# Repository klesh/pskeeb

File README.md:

# Portable Split Keyboard

## Features

- Tenting design - good for RSI symptoms
- Stackable - portable
- 36 keys columnar layout - less movement when typing
- Trackpoint support

## Designs

- [pskeeb1 gateron ks27](pskeeb1_gateron_ks27): Mainly designed for Gateron KS27 low profile switches, Blackpill controller, Diodeless
- [pskeeb2 express](pskeeb2_express): All Kinds of switches, Blackpill controller, Diodeless, 9.2x9.2cm PCB
- [pskeeb3 cherry hotswap](pskeeb3_cherry_hotswap): Cherry MX Switch, Raspberry Pi Pico, Diodeless
- [pskeeb4 gateron low profile ks27 hotswap](pskeeb4_gtr_lp_ks27_hotswap): Gateron Low Profile Switch, RP2040-Zero
- [pskeeb5 bluetooth kaihl choc v1/v2 hotswap](pskeeb5_bluetooth_choc_hotswap): Kaihl Choc v1/v2 Low Profile Switch, nice!nano v2

## Assembly

#### Trackpoint

1. Follow [this great guide](https://github.com/alonswartz/trackpoint#q-how-do-i-identify-the-trackpoint-pinout) and [this topic](https://geekhack.org/index.php?topic=115912.0) to identify the trackpoint pinout
2. Solder GH cable to the trackpoint by refering to the socket wiring sequence: RST/DAT/CLK/GND/VCC (top to bottom)

## Developement

```
git clone https://github.com/klesh/pskeeb.git
git submodule update --init --recursive
```

Use the following options when exporting gerber for JLCPCB manufactoring.

# License
This work is licensed under a Creative Commons Attribution-NonCommercial-ShareAlike 4.0 International License.

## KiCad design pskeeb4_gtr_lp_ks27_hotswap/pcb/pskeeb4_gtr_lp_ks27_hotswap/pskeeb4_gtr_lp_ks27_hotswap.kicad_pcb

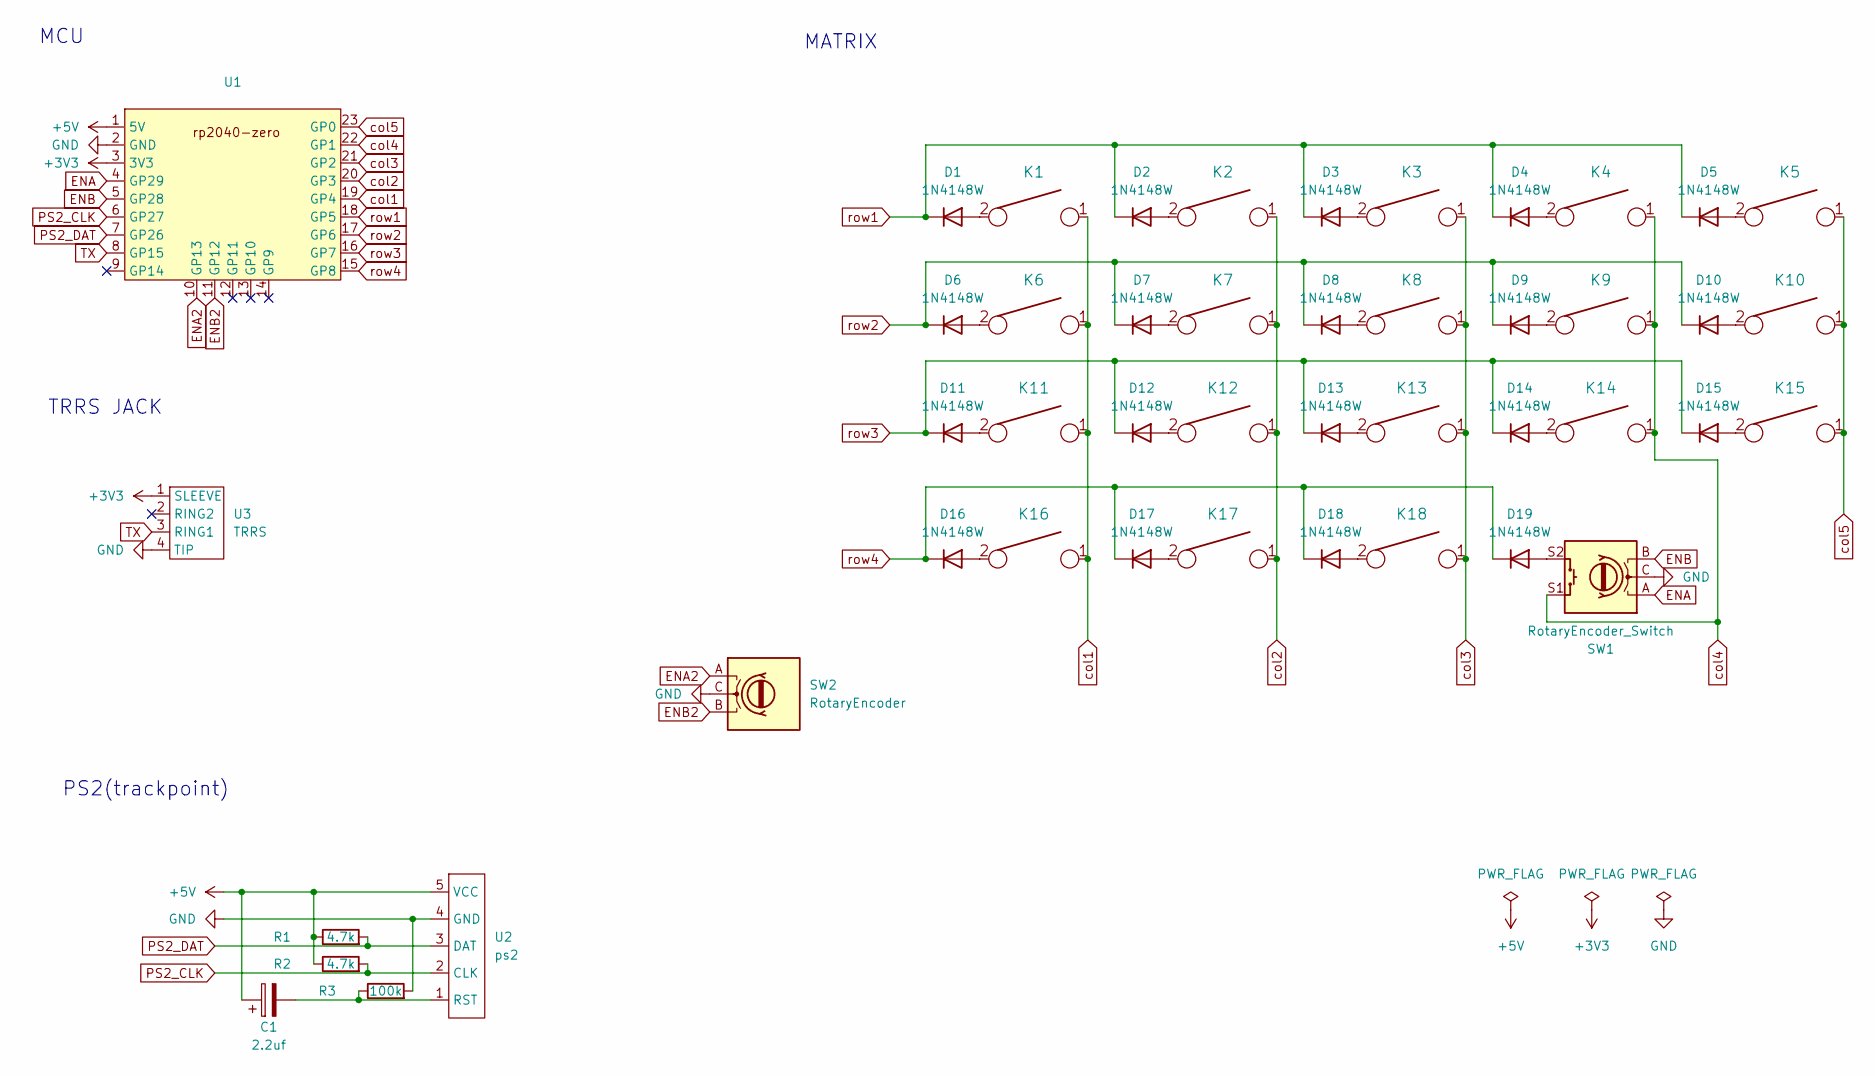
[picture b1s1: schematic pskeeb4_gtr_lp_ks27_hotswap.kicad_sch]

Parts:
C1: 2.2uf; C_1206_3216Metric_Pad1.33x1.80mm_HandSolder
D1, D2, D3, D4, D5, D6, D7, D8, D9, D10, D11, D12, D13, D14, D15, D16, D17, D18, D19: 1N4148W; D_SOD-123 Reversible
K1, K2, K3, K4, K5, K6, K7, K8, K9, K10, K11, K12, K13, K14, K15, K16, K17, K18: KEYSW; Gateron KS-27 Hotswap Reversible
R1, R2: 4.7k; C_1206_3216Metric_Pad1.33x1.80mm_HandSolder
R3: 100k; C_1206_3216Metric_Pad1.33x1.80mm_HandSolder
SW1: RotaryEncoder_Switch; E8H8 Rotary Encoder Reversible
SW2: RotaryEncoder; nobole-rotary-encoder
U1: RP2024-Zero
U2: ps2; JST_GH_BM05B-GHS-TBT_1x05-1MP_P1.25mm_Vertical
U3: TRRS; TRRS-PJ-320D Reversible

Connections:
+3V3: U1.3 (3V3), U3.1 (SLEEVE)
+5V: C1.1, R1.1, R2.1, U1.1 (5V), U2.5 (VCC)
ENA: SW1.A, U1.4 (GP29)
ENA2: SW2.A, U1.10 (GP13)
ENB: SW1.B, U1.5 (GP28)
ENB2: SW2.B, U1.11 (GP12)
GND: R3.2, SW1.C, SW2.C, U1.2 (GND), U2.4 (GND), U3.4 (TIP)
unnamed: D1.2 (A), K1.2
unnamed: D2.2 (A), K2.2
unnamed: D3.2 (A), K3.2
unnamed: D4.2 (A), K4.2
unnamed: D5.2 (A), K5.2
unnamed: D6.2 (A), K6.2
unnamed: D7.2 (A), K7.2
unnamed: D8.2 (A), K8.2
unnamed: D9.2 (A), K9.2
unnamed: D10.2 (A), K10.2
unnamed: D11.2 (A), K11.2
unnamed: D12.2 (A), K12.2
unnamed: D13.2 (A), K13.2
unnamed: D14.2 (A), K14.2
unnamed: D15.2 (A), K15.2
unnamed: D16.2 (A), K16.2
unnamed: D17.2 (A), K17.2
unnamed: D18.2 (A), K18.2
unnamed: D19.2 (A), SW1.S2
unnamed: C1.2, R3.1, U2.1 (RST)
PS2_CLK: R2.2, U1.6 (GP27), U2.2 (CLK)
PS2_DAT: R1.2, U1.7 (GP26), U2.3 (DAT)
TX: U1.8 (GP15), U3.3 (RING1)
col1: K1.1, K6.1, K11.1, K16.1, U1.19 (GP4)
col2: K2.1, K7.1, K12.1, K17.1, U1.20 (GP3)
col3: K3.1, K8.1, K13.1, K18.1, U1.21 (GP2)
col4: K4.1, K9.1, K14.1, SW1.S1, U1.22 (GP1)
col5: K5.1, K10.1, K15.1, U1.23 (GP0)
row1: D1.1 (K), D2.1 (K), D3.1 (K), D4.1 (K), D5.1 (K), U1.18 (GP5)
row2: D6.1 (K), D7.1 (K), D8.1 (K), D9.1 (K), D10.1 (K), U1.17 (GP6)
row3: D11.1 (K), D12.1 (K), D13.1 (K), D14.1 (K), D15.1 (K), U1.16 (GP7)
row4: D16.1 (K), D17.1 (K), D18.1 (K), D19.1 (K), U1.15 (GP8)

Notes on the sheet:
MATRIX
MCU
TRRS JACK
PS2(trackpoint)

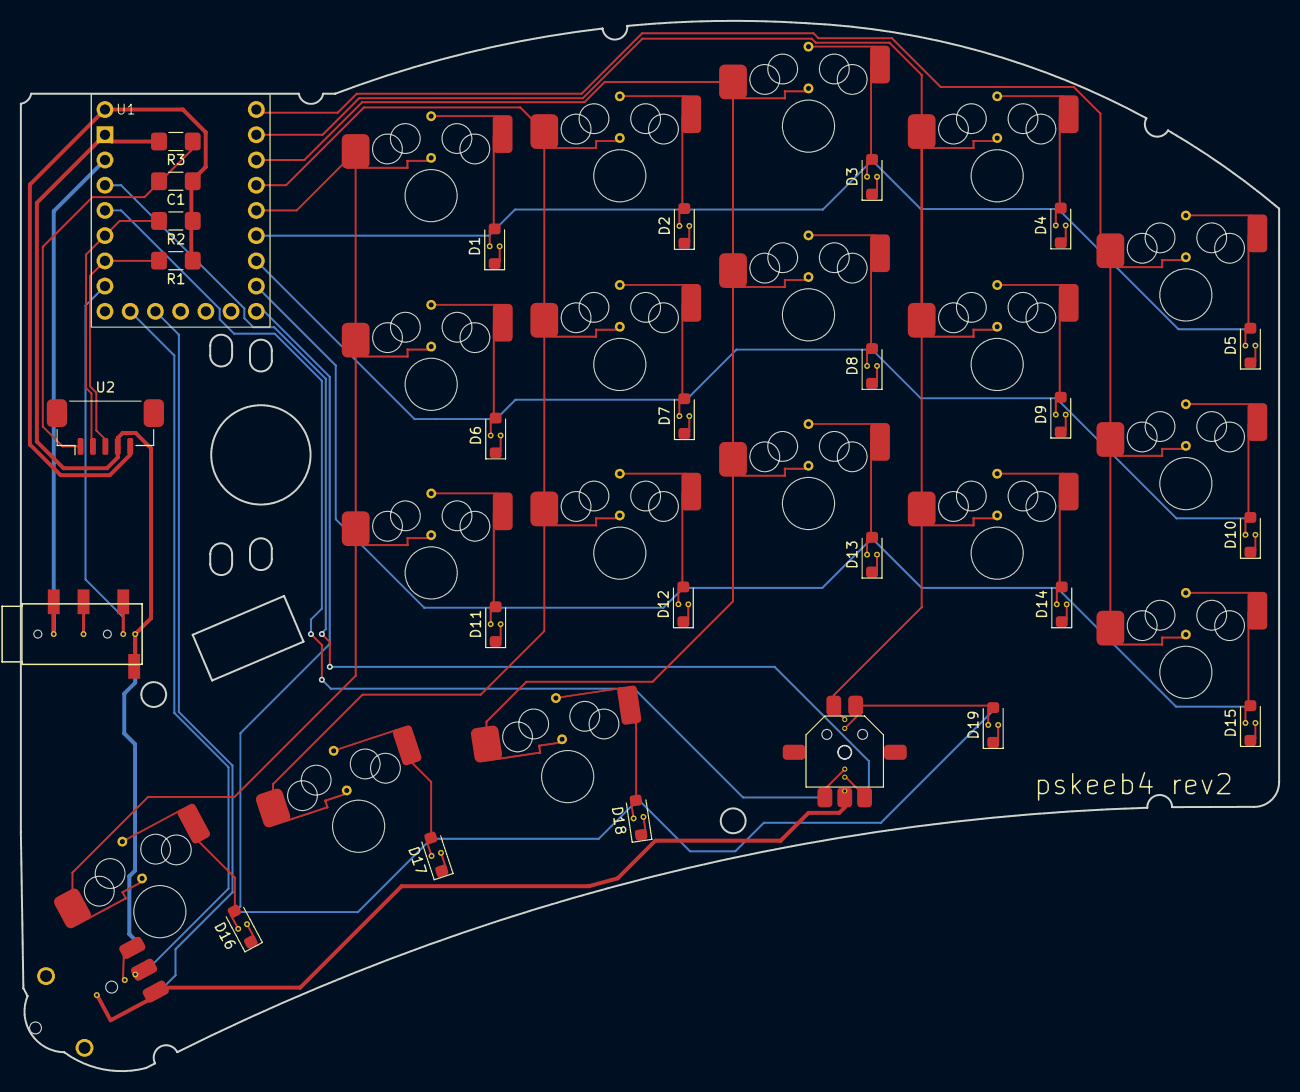
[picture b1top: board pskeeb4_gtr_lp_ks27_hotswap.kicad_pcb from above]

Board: 2 copper layers, 126.7 x 105.8 mm, 46 parts (0 on the bottom side), 39 nets.

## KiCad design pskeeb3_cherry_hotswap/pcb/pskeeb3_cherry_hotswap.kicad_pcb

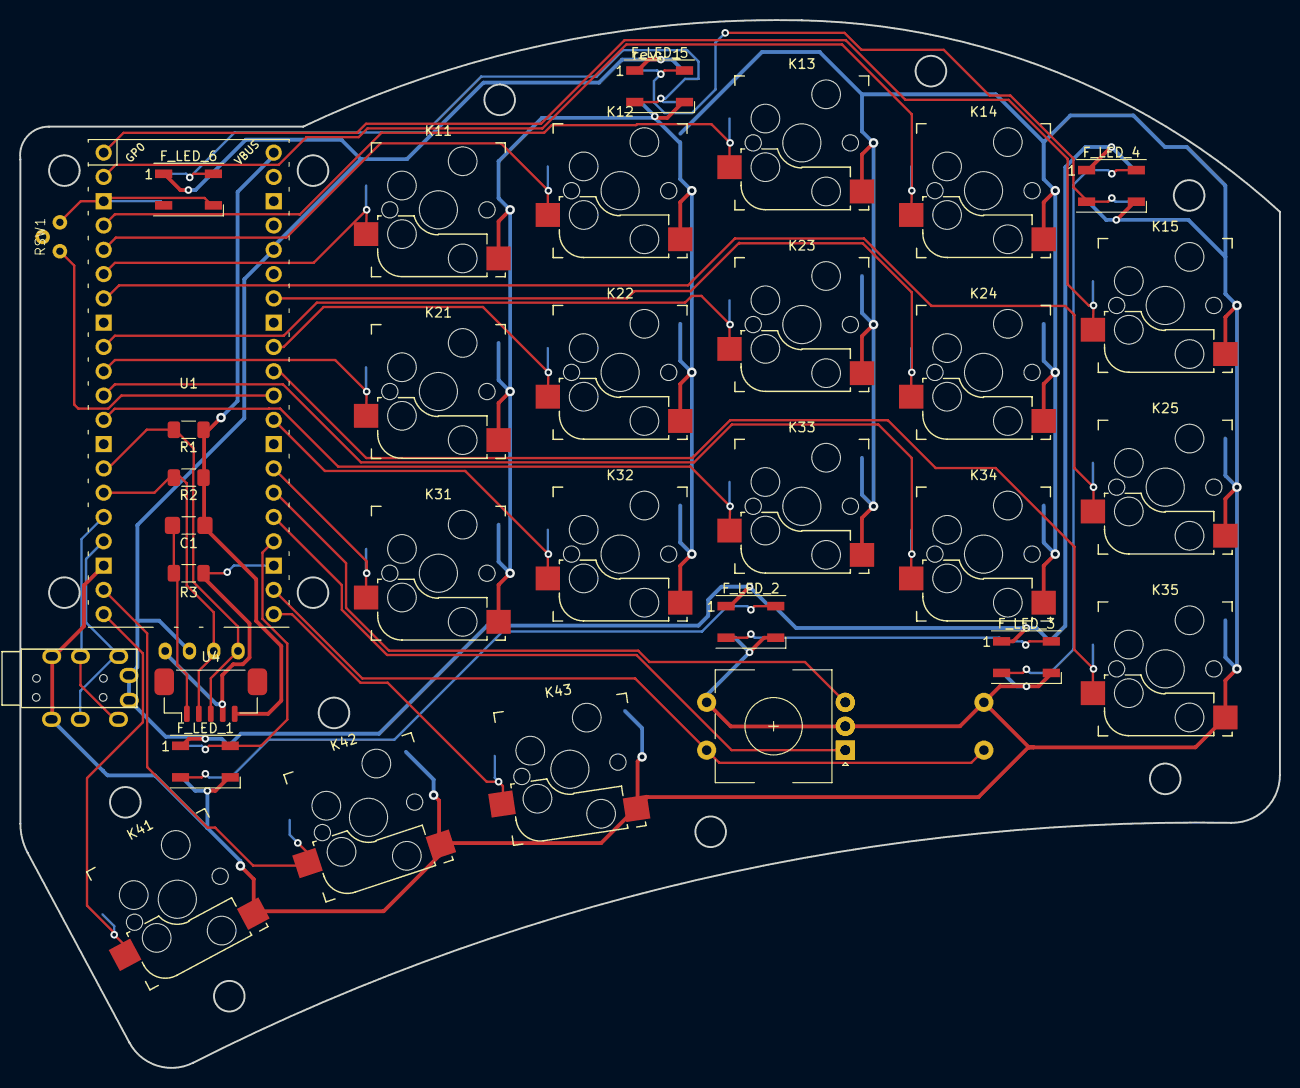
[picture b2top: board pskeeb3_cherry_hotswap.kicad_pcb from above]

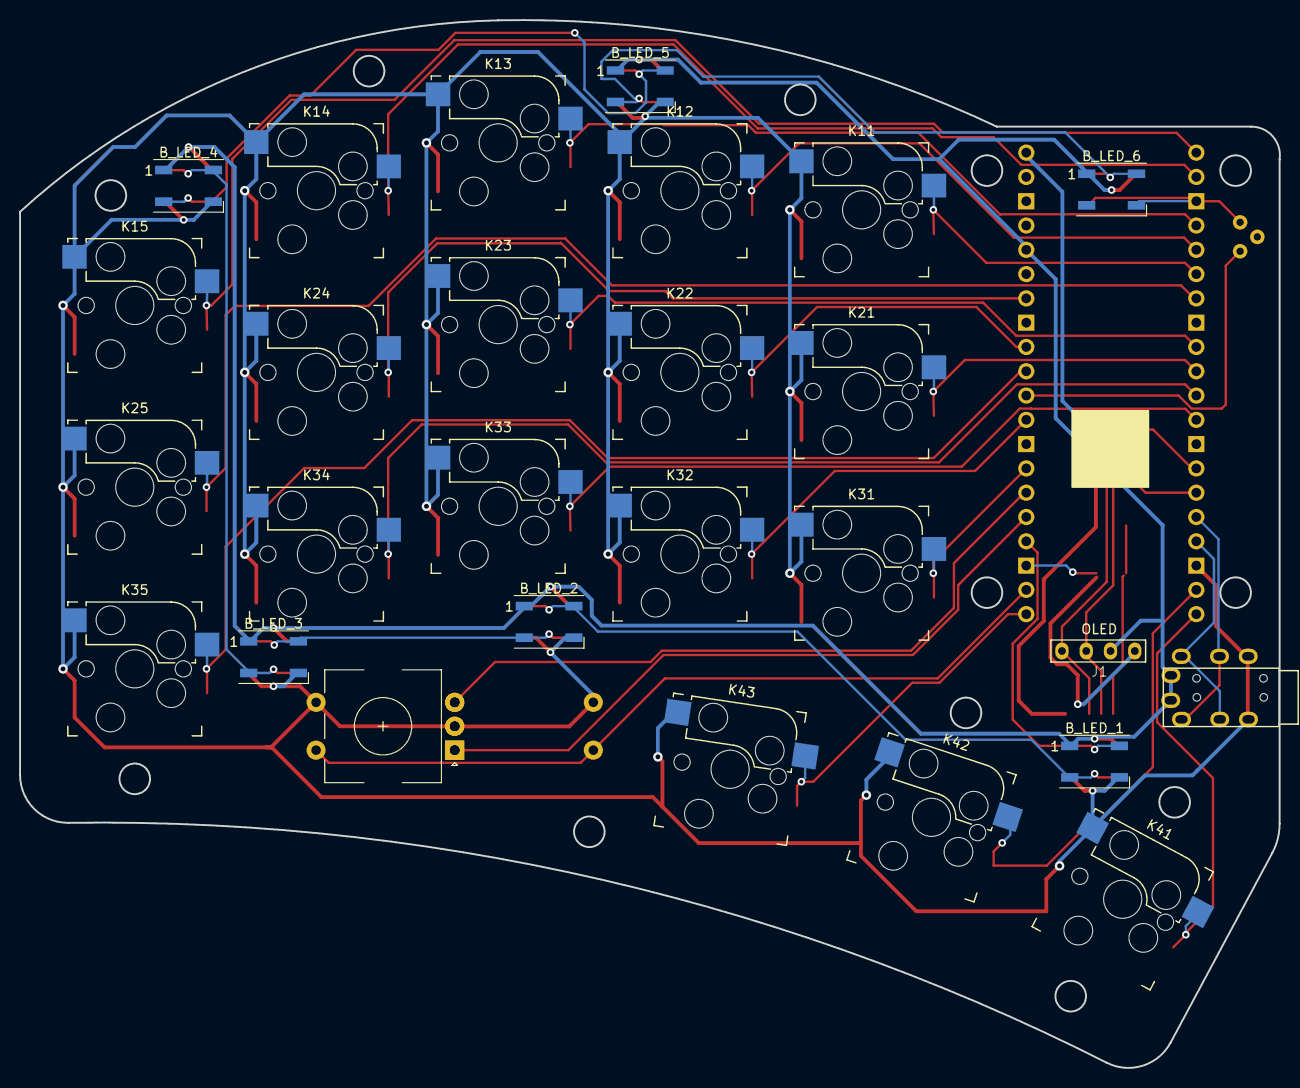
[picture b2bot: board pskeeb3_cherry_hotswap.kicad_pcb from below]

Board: 2 copper layers, 131.7 x 109.6 mm, 42 parts (9 on the bottom side), 38 nets.

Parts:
B_LED_1, B_LED_2, B_LED_3, B_LED_4, B_LED_5, B_LED_6: WS2812B; LED_WS2812B_PLCC4_5.0x5.0mm_P3.2mm
C1: 2.2uf; C_1206_3216Metric_Pad1.33x1.80mm_HandSolder
F_LED_1, F_LED_2, F_LED_3, F_LED_4, F_LED_5, F_LED_6: WS2812B; LED_WS2812B_PLCC4_5.0x5.0mm_P3.2mm
J1: OLED
K11, K12, K13, K14, K15, K21, K22, K23, K24, K25, K31, K32, K33, K34, K35, K41, K42, K43: KEYSW; Kailh_socket_MX_reversible
R1, R2: 4.7k; R_1206_3216Metric_Pad1.30x1.75mm_HandSolder
R3: 100k; R_1206_3216Metric_Pad1.30x1.75mm_HandSolder
RSW1: SW_PUSH; 4.5x4.5x5side-switch
SW1, SW2: RotaryEncoder_Switch; RotaryEncoder_EC11-no-legs
U1: Pico; RPi_Pico_TH
U2, U3: TRRS; TRRS-PJ-320A
U4: trackpoint; JST_GH_BM05B-GHS-TBT_1x05-1MP_P1.25mm_Vertical

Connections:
+3V3: B_LED_1.1 (VDD), B_LED_2.1 (VDD), B_LED_3.1 (VDD), B_LED_4.1 (VDD), B_LED_5.1 (VDD), B_LED_6.1 (VDD), F_LED_1.1 (VDD), F_LED_2.1 (VDD), F_LED_3.1 (VDD), F_LED_4.1 (VDD), F_LED_5.1 (VDD), F_LED_6.1 (VDD), J1.3, U1.36 (3V3), U2.1 (SLEEVE), U3.1 (SLEEVE)
+5V: C1.1, R1.1, R2.1, U1.40 (VBUS), U4.5 (VCC)
/k11: K11.2, U1.6 (GPIO4)
/k12: K12.2, U1.5 (GPIO3)
/k13: K13.2, U1.4 (GPIO2)
/k14: K14.2, U1.2 (GPIO1)
/k15: K15.2, U1.1 (GPIO0)
/k21: K21.2, U1.10 (GPIO7)
/k22: K22.2, U1.32 (GPIO27_ADC1)
/k23: K23.2, U1.9 (GPIO6)
/k24: K24.2, U1.34 (GPIO28_ADC2)
/k25: K25.2, U1.7 (GPIO5)
/k31: K31.2, U1.27 (GPIO21)
/k32: K32.2, U1.29 (GPIO22)
/k33: K33.2, U1.12 (GPIO9)
/k34: K34.2, U1.11 (GPIO8)
/k35: K35.2, U1.31 (GPIO26_ADC0)
/k41: K41.2, U1.20 (GPIO15)
/k42: K42.2, U1.19 (GPIO14)
/k43: K43.2, U1.21 (GPIO16)
/k44: SW1.S2, SW2.S2, U1.22 (GPIO17)
ENA: SW1.A, SW2.A, U1.25 (GPIO19)
ENB: SW1.B, SW2.B, U1.26 (GPIO20)
GND: B_LED_1.3 (VSS), B_LED_2.3 (VSS), B_LED_3.3 (VSS), B_LED_4.3 (VSS), B_LED_5.3 (VSS), F_LED_1.3 (VSS), F_LED_2.3 (VSS), F_LED_3.3 (VSS), F_LED_4.3 (VSS), F_LED_5.3 (VSS), K11.1, K12.1, K13.1, K14.1, K15.1, K21.1, K22.1, K23.1, K24.1, K25.1, K31.1, K32.1, K33.1, K34.1, K35.1, K41.1, K42.1, K43.1, SW1.C, SW1.S1, SW2.C, SW2.S1, U1.18 (GND), U2.4 (TIP), U3.4 (TIP)
GND1: J1.4, R3.2, U1.23 (GND), U4.4 (GND)
GND2: B_LED_6.3 (VSS), F_LED_6.3 (VSS), RSW1.2, U1.3 (GND)
LED: B_LED_1.4 (DIN), F_LED_1.4 (DIN), U1.24 (GPIO18)
unnamed: B_LED_1.2 (DOUT), B_LED_2.4 (DIN), F_LED_1.2 (DOUT), F_LED_2.4 (DIN)
unnamed: B_LED_2.2 (DOUT), B_LED_3.4 (DIN), F_LED_2.2 (DOUT), F_LED_3.4 (DIN)
unnamed: B_LED_3.2 (DOUT), B_LED_4.4 (DIN), F_LED_3.2 (DOUT), F_LED_4.4 (DIN)
unnamed: B_LED_4.2 (DOUT), B_LED_5.4 (DIN), F_LED_4.2 (DOUT), F_LED_5.4 (DIN)
unnamed: B_LED_5.2 (DOUT), B_LED_6.4 (DIN), F_LED_5.2 (DOUT), F_LED_6.4 (DIN)
RX: U1.17 (GPIO13), U2.2 (RING2), U3.3 (RING1)
TP_CLK/I2C1_SCL: J1.2, R2.2, U1.15 (GPIO11), U4.2 (CLK)
TP_DAT/I2C1_SDA: J1.1, R1.2, U1.14 (GPIO10), U4.3 (DAT)
TP_RST: C1.2, R3.1, U4.1 (RST)
TX: U1.16 (GPIO12), U2.3 (RING1), U3.2 (RING2)
run: RSW1.1, U1.30 (RUN)

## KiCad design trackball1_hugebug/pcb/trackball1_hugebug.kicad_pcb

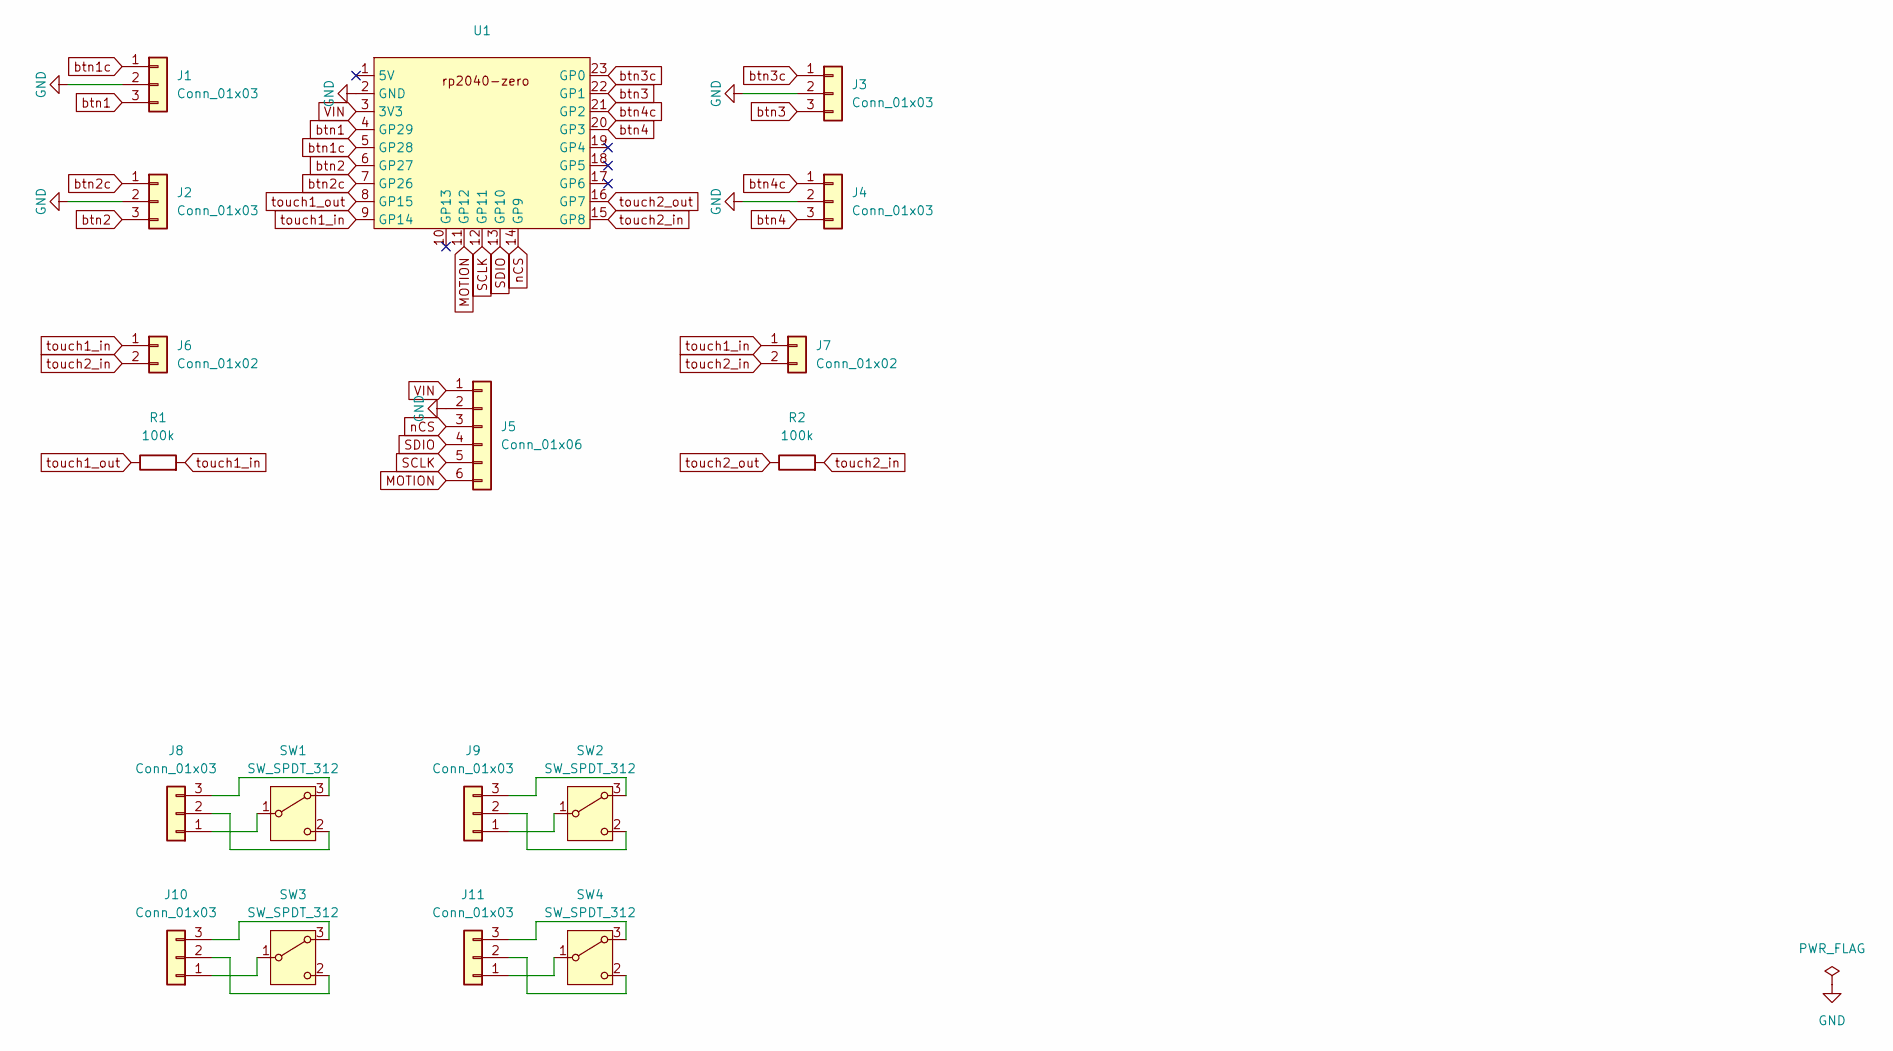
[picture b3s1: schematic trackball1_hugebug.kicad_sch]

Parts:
J1, J2, J3, J4: Conn_01x03; JST_GH_BM03B-GHS-TBT_1x03-1MP_P1.25mm_Vertical
J5: Conn_01x06; JST_GH_BM06B-GHS-TBT_1x06-1MP_P1.25mm_Vertical
J6, J7: Conn_01x02; JST_GH_BM02B-GHS-TBT_1x02-1MP_P1.25mm_Vertical
J8, J9, J10, J11: Conn_01x03; PinHeader_1x03_P2.00mm_Vertical
R1, R2: 100k; R_1206_3216Metric
SW1, SW2, SW3, SW4: SW_SPDT_312; MouseSwitch
U1: RP2024-Zero

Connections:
GND: J1.2, J2.2, J3.2, J4.2, J5.2, U1.2 (GND)
MOTION: J5.6, U1.11 (GP12)
unnamed: J8.1, SW1.1 (B)
unnamed: J8.2, SW1.2 (C)
unnamed: J8.3, SW1.3 (A)
unnamed: J9.1, SW2.1 (B)
unnamed: J9.2, SW2.2 (C)
unnamed: J9.3, SW2.3 (A)
unnamed: J10.1, SW3.1 (B)
unnamed: J10.2, SW3.2 (C)
unnamed: J10.3, SW3.3 (A)
unnamed: J11.1, SW4.1 (B)
unnamed: J11.2, SW4.2 (C)
unnamed: J11.3, SW4.3 (A)
SCLK: J5.5, U1.12 (GP11)
SDIO: J5.4, U1.13 (GP10)
VIN: J5.1, U1.3 (3V3)
btn1: J1.3, U1.4 (GP29)
btn1c: J1.1, U1.5 (GP28)
btn2: J2.3, U1.6 (GP27)
btn2c: J2.1, U1.7 (GP26)
btn3: J3.3, U1.22 (GP1)
btn3c: J3.1, U1.23 (GP0)
btn4: J4.3, U1.20 (GP3)
btn4c: J4.1, U1.21 (GP2)
nCS: J5.3, U1.14 (GP9)
touch1_in: J6.1, J7.1, R1.2, U1.9 (GP14)
touch1_out: R1.1, U1.8 (GP15)
touch2_in: J6.2, J7.2, R2.2, U1.15 (GP8)
touch2_out: R2.1, U1.16 (GP7)

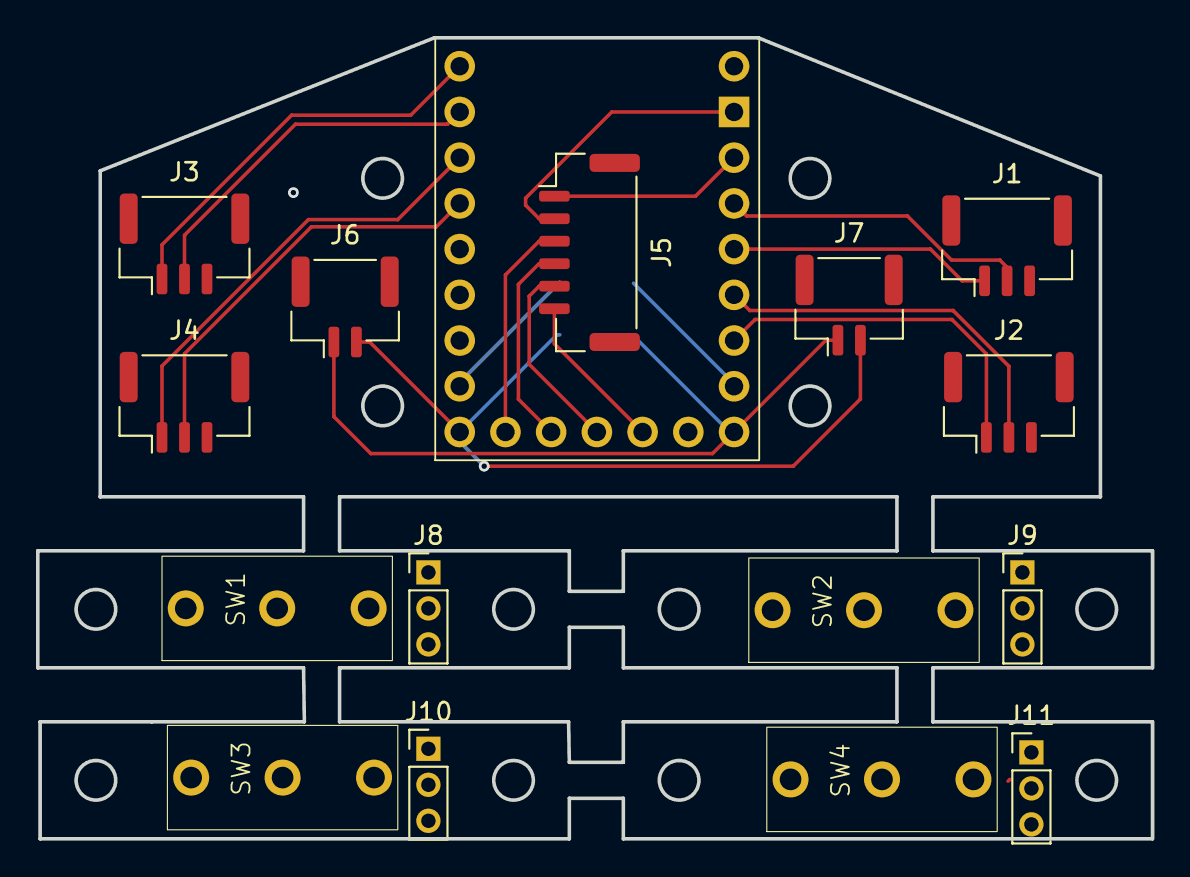
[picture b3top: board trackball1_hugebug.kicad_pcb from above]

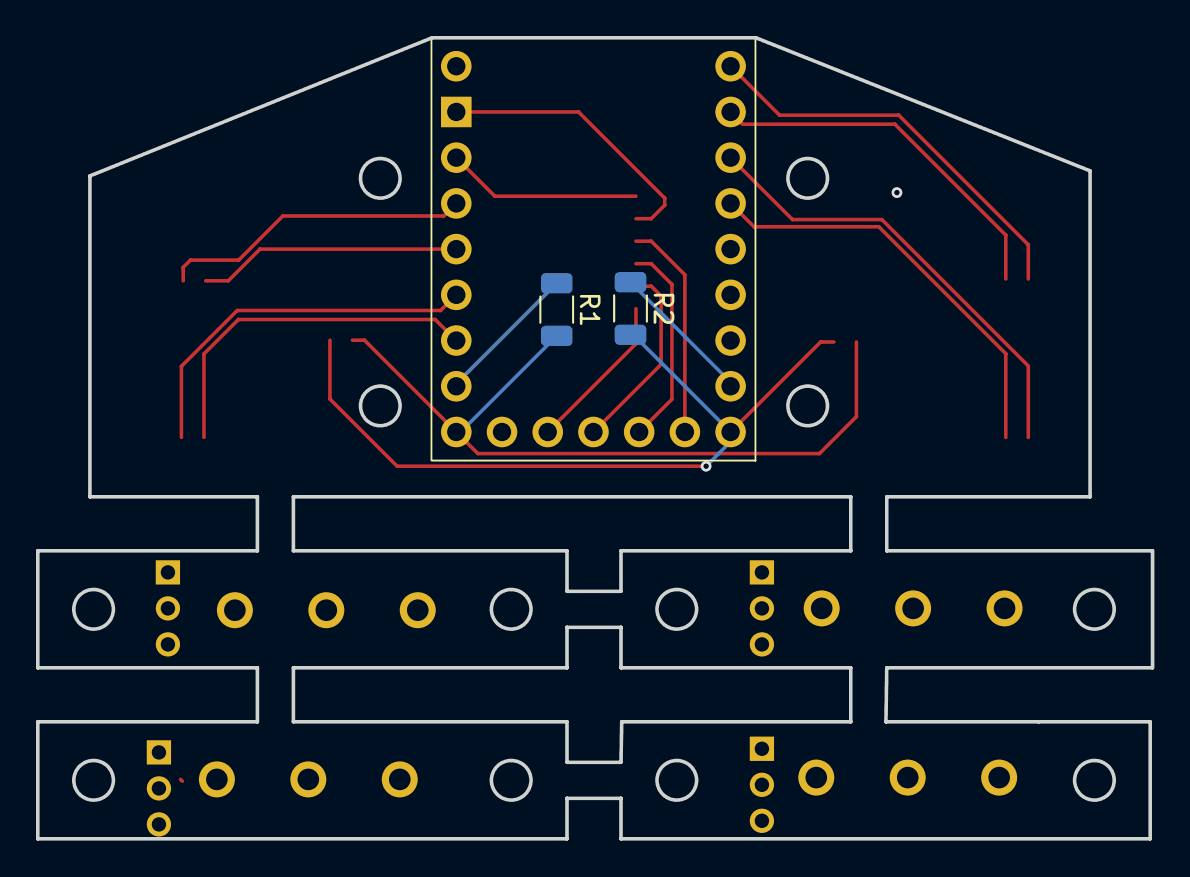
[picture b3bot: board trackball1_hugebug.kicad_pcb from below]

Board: 2 copper layers, 61.9 x 44.5 mm, 18 parts (3 on the bottom side), 30 nets.

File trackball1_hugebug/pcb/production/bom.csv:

Designator,Footprint,Quantity,Value,LCSC Part #
"J1, J2, J3, J4",JST_GH_BM03B-GHS-TBT_1x03-1MP_P1.25mm_Vertical,4,Conn_01x03,
"J10, J11, J8, J9",PinHeader_1x03_P2.00mm_Vertical,4,Conn_01x03,
J5,Hirose_FH12-8S-0.5SH_1x08-1MP_P0.50mm_Horizontal,1,Conn_01x08,
"J6, J7",JST_GH_BM02B-GHS-TBT_1x02-1MP_P1.25mm_Vertical,2,Conn_01x02,
"R1, R2",1206,2,100k,
"SW1, SW2, SW3, SW4",MouseSwitch,4,SW_SPDT,
U1,RP2024-Zero,1,~,

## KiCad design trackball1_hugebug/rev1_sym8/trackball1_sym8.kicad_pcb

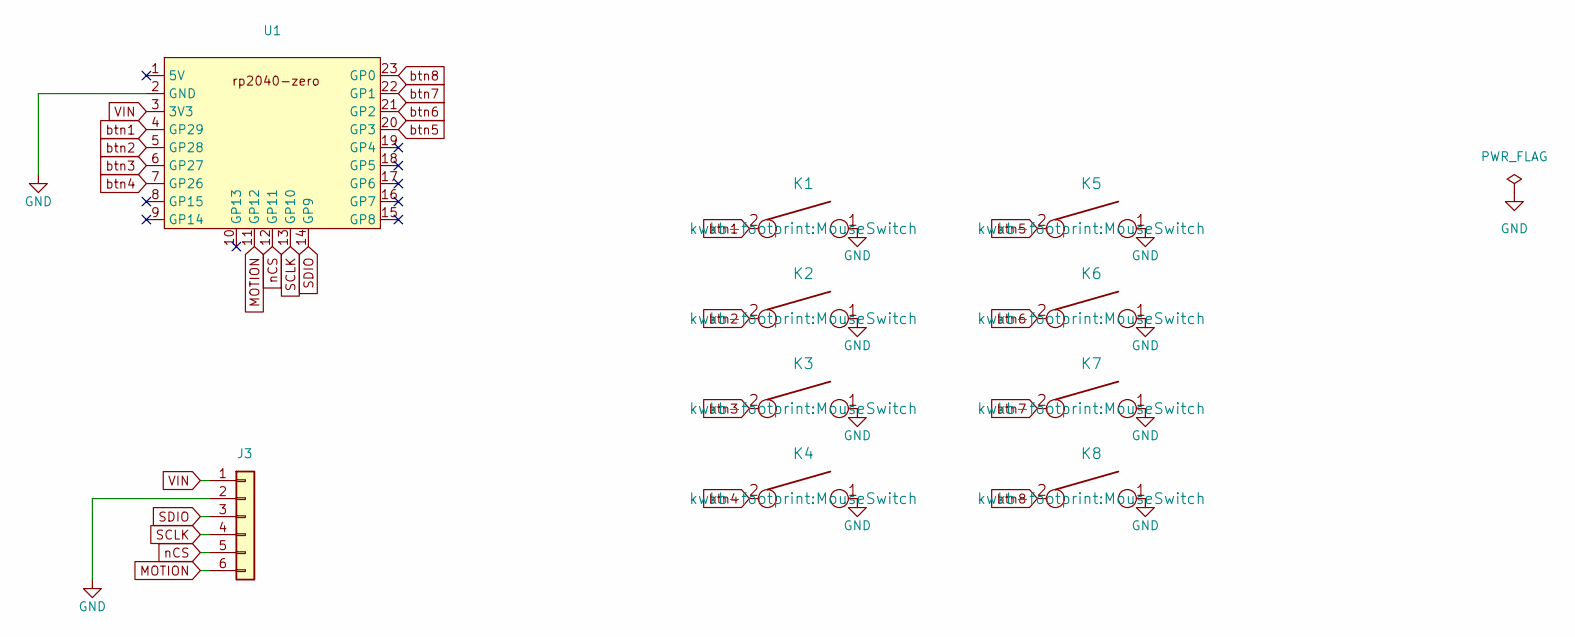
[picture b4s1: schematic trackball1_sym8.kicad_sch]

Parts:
J3: Conn_01x06; PinHeader_1x06_P2.54mm_Vertical
K1, K2, K3, K4, K5, K6, K7, K8: KEYSW; MouseSwitch
U1: RP2024-Zero

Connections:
GND: J3.2, K1.1, K2.1, K3.1, K4.1, K5.1, K6.1, K7.1, K8.1, U1.2 (GND)
MOTION: J3.6, U1.11 (GP12)
SCLK: J3.4, U1.13 (GP10)
SDIO: J3.3, U1.14 (GP9)
VIN: J3.1, U1.3 (3V3)
btn1: K1.2, U1.4 (GP29)
btn2: K2.2, U1.5 (GP28)
btn3: K3.2, U1.6 (GP27)
btn4: K4.2, U1.7 (GP26)
btn5: K5.2, U1.20 (GP3)
btn6: K6.2, U1.21 (GP2)
btn7: K7.2, U1.22 (GP1)
btn8: K8.2, U1.23 (GP0)
nCS: J3.5, U1.12 (GP11)

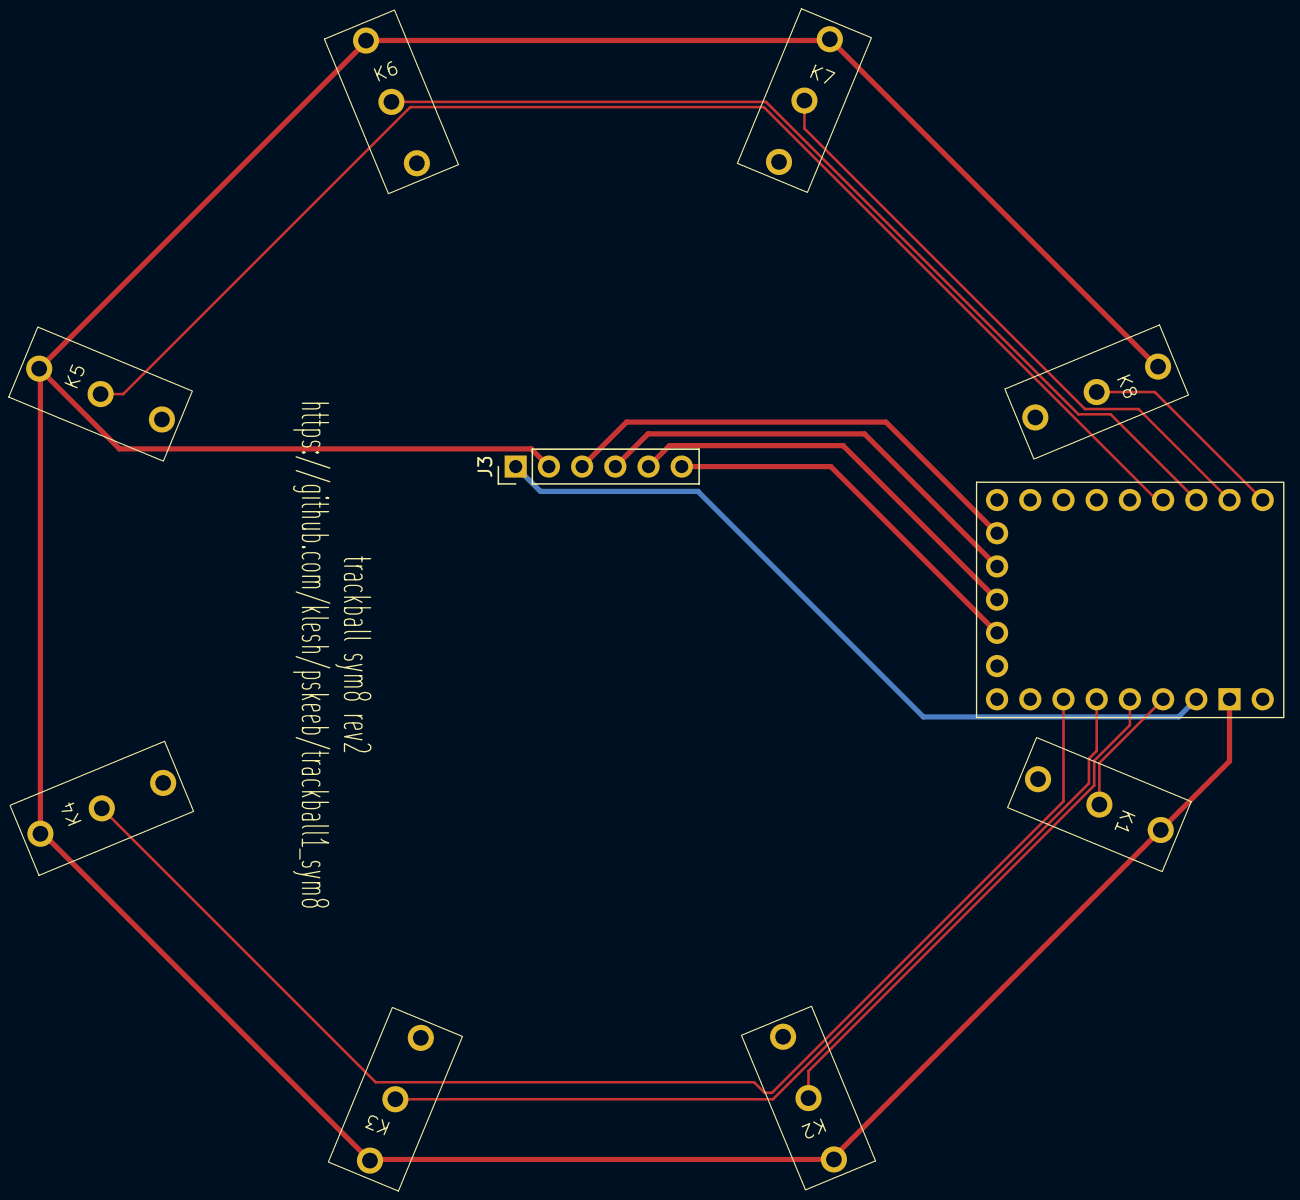
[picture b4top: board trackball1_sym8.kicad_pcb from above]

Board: 2 copper layers, 10 parts (1 on the bottom side), 14 nets.

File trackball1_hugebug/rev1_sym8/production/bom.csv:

Designator,Footprint,Quantity,Value,LCSC Part #
J3,PinHeader_1x06_P2.54mm_Vertical,1,Conn_01x06,
"K1, K2, K3, K4, K5, K6, K7, K8",MouseSwitch,8,KEYSW,
U1,RP2024-Zero,1,~,

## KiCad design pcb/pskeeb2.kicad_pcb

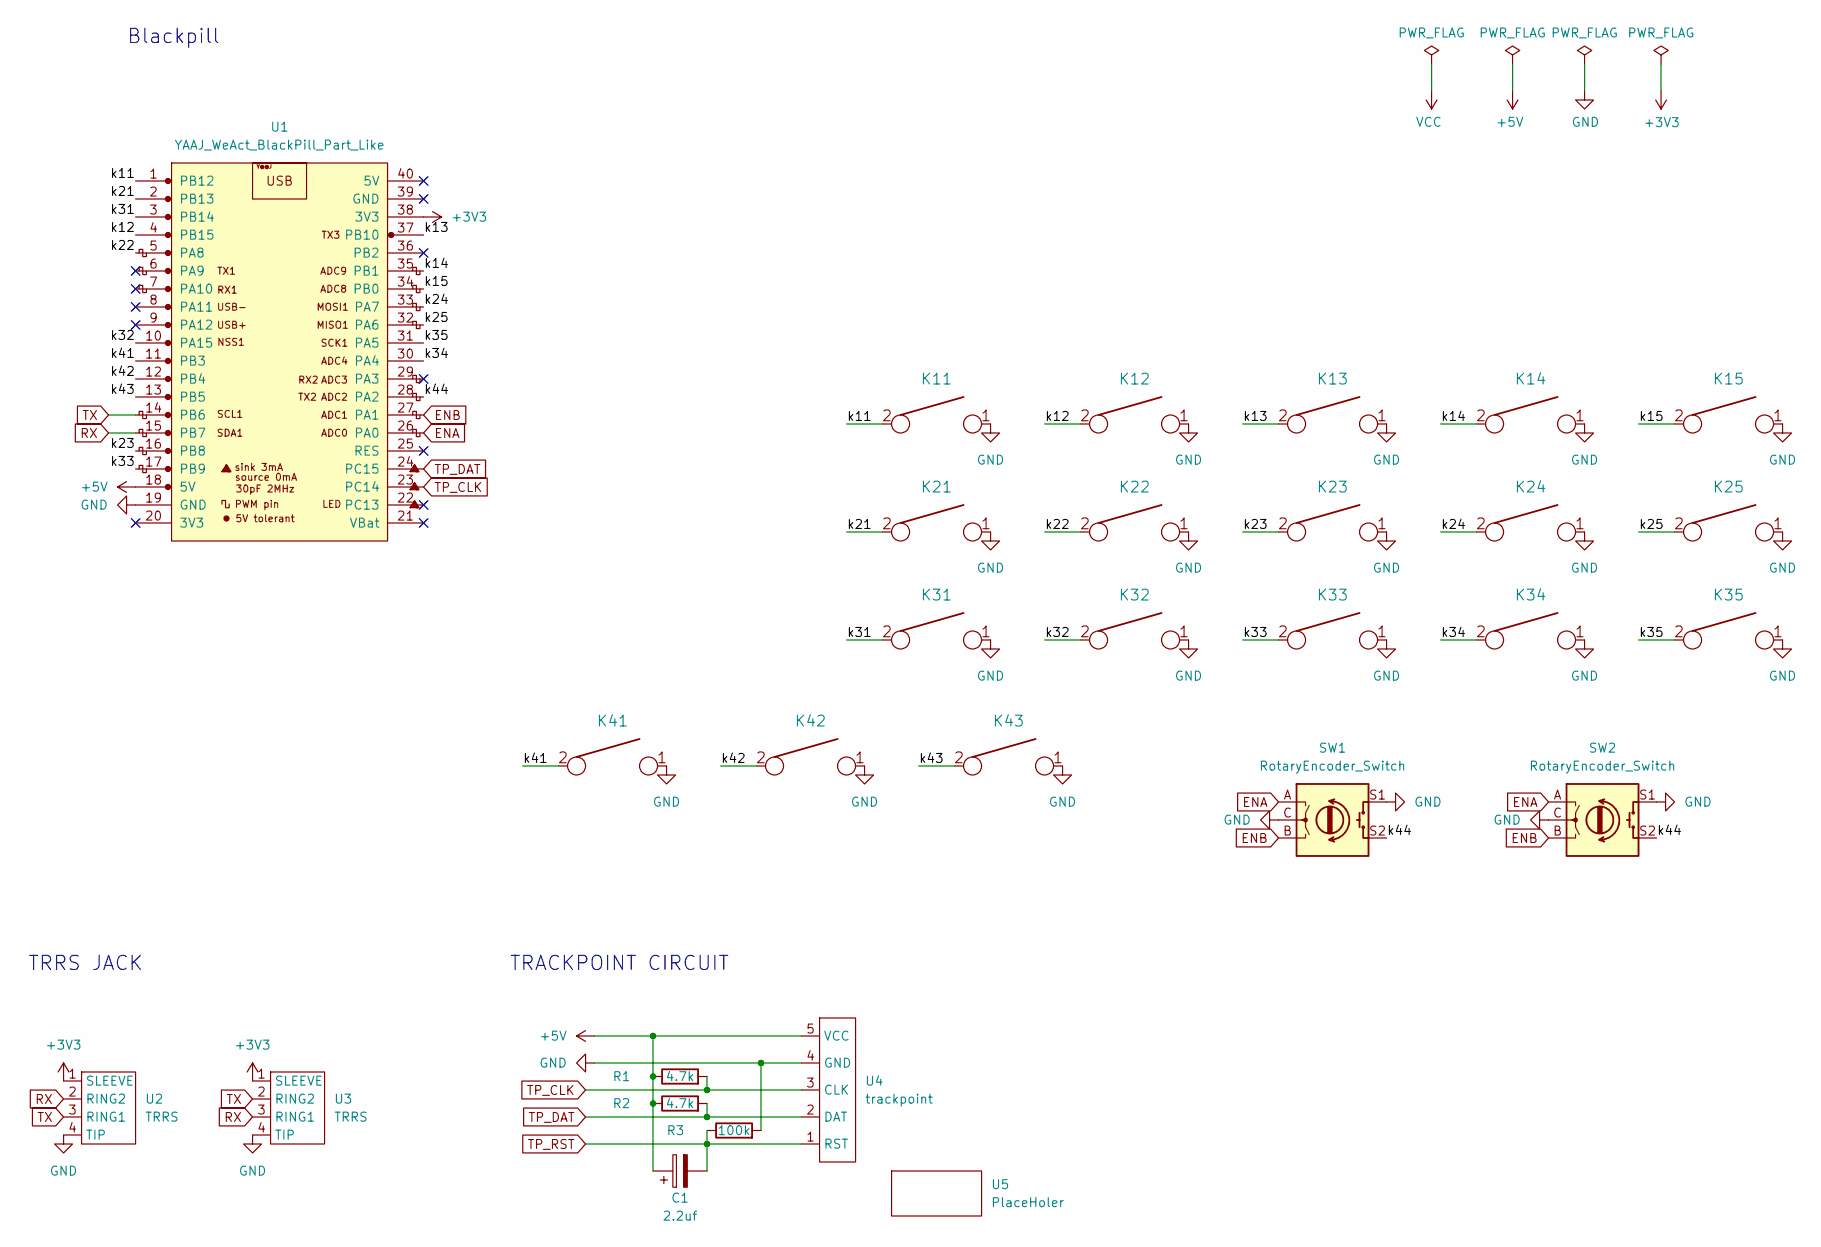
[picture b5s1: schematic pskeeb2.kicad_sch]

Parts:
C1: 2.2uf; C_1206_3216Metric_Pad1.33x1.80mm_HandSolder
K11, K12, K13, K14, K15, K21, K22, K23, K24, K25, K31, K32, K33, K34, K35, K41, K42, K43: KEYSW; Mx-Choc-Rev
R1, R2: 4.7k; R_1206_3216Metric_Pad1.30x1.75mm_HandSolder
R3: 100k; R_1206_3216Metric_Pad1.30x1.75mm_HandSolder
SW1, SW2: RotaryEncoder_Switch; RotaryEncoder_EC11-no-legs
U1: YAAJ_WeAct_BlackPill_Part_Like; YAAJ_WeAct_BlackPill_2
U2, U3: TRRS; TRRS-PJ-320A
U4: trackpoint; JST_GH_SM05B-GHS-TB_1x05-1MP_P1.25mm_Horizontal
U5: PlaceHoler; T400-Trackpoint-mix

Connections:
/k11: K11.2, U1.1 (PB12)
/k12: K12.2, U1.4 (PB15)
/k13: K13.2, U1.37 (PB10)
/k14: K14.2, U1.35 (PB1)
/k15: K15.2, U1.34 (PB0)
/k21: K21.2, U1.2 (PB13)
/k22: K22.2, U1.5 (PA8)
/k23: K23.2, U1.16 (PB8)
/k24: K24.2, U1.33 (PA7)
/k25: K25.2, U1.32 (PA6)
/k31: K31.2, U1.3 (PB14)
/k32: K32.2, U1.10 (PA15)
/k33: K33.2, U1.17 (PB9)
/k34: K34.2, U1.30 (PA4)
/k35: K35.2, U1.31 (PA5)
/k41: K41.2, U1.11 (PB3)
/k42: K42.2, U1.12 (PB4)
/k43: K43.2, U1.13 (PB5)
/k44: SW1.S2, SW2.S2, U1.28 (PA2)
ENA: SW1.A, SW2.A, U1.26 (PA0)
ENB: SW1.B, SW2.B, U1.27 (PA1)
RX: U1.15 (PB7), U2.2 (RING2), U3.3 (RING1)
TP_CLK: R1.2, U1.23 (PC14), U4.3 (CLK)
TP_DAT: R2.2, U1.24 (PC15), U4.2 (DAT)
TP_RST: C1.2, R3.1, U4.1 (RST)
TX: U1.14 (PB6), U2.3 (RING1), U3.2 (RING2)

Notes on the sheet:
TRRS JACK
Blackpill
TRACKPOINT CIRCUIT

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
